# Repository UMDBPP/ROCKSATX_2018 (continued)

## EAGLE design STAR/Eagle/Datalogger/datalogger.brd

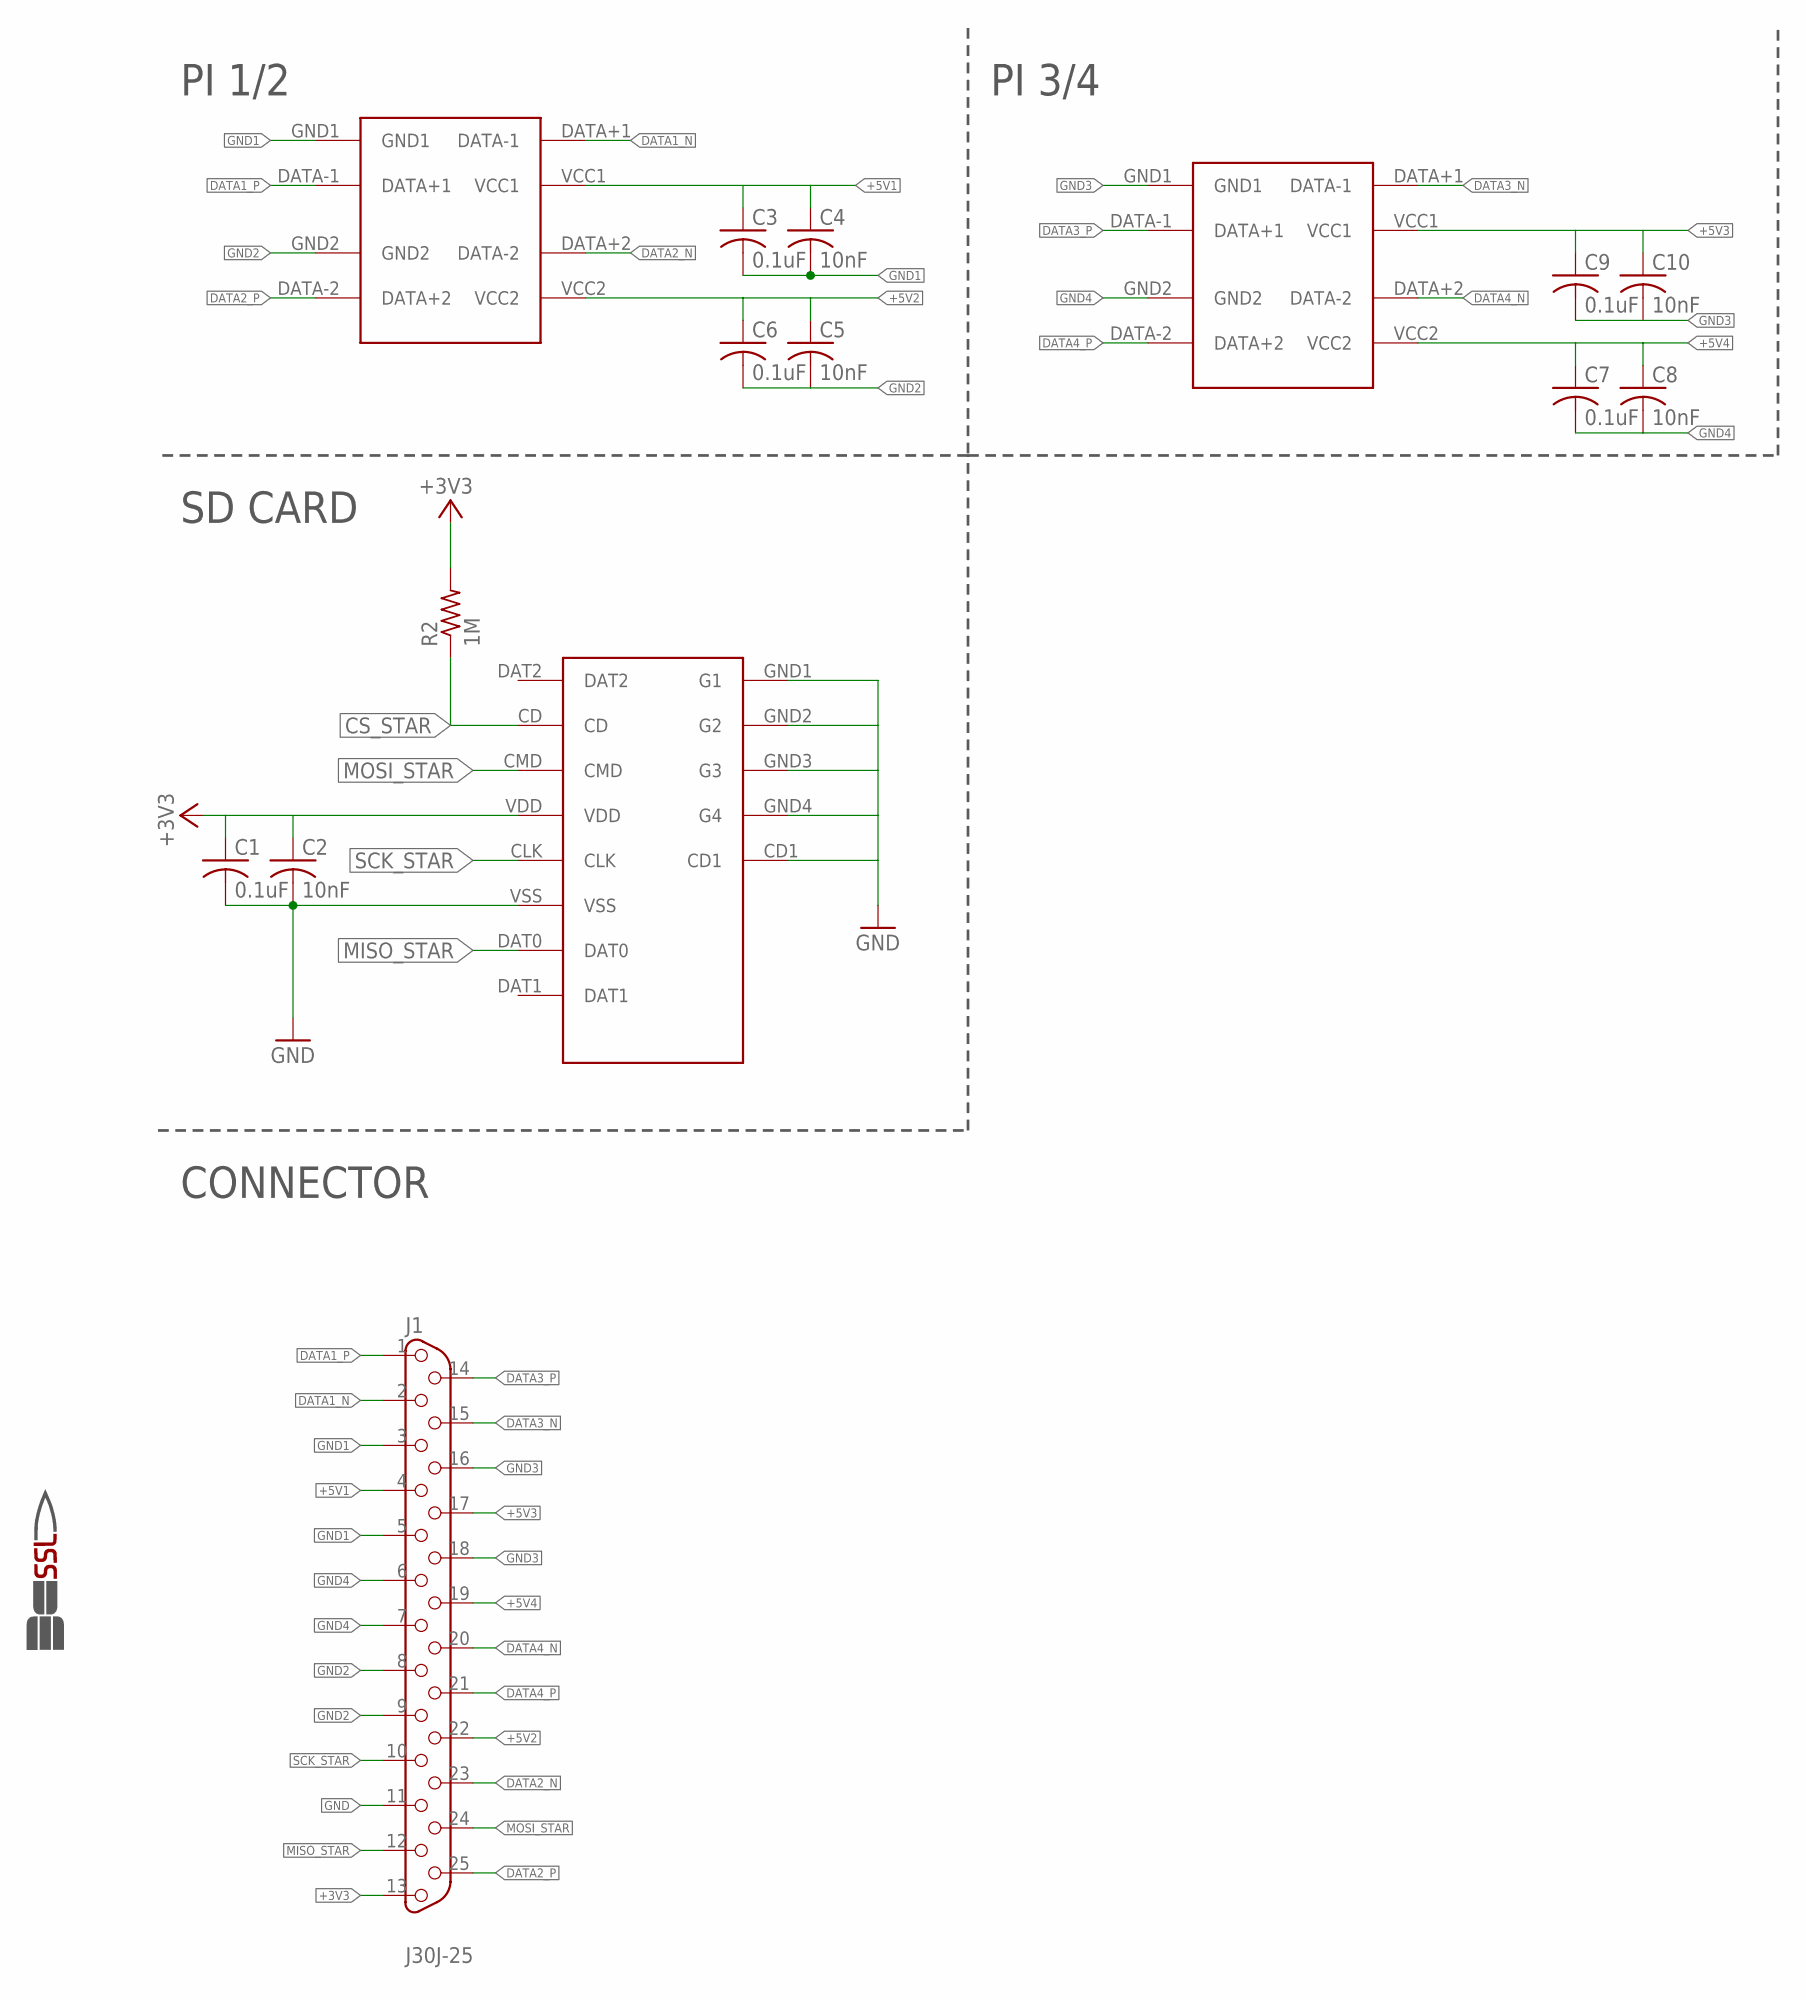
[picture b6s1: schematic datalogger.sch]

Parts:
C1, C3, C6, C7, C9: 0.1uF; C0603
C2, C4, C5, C8, C10: 10nF; C0603
GND1: SSL.3IN_SILK; SSL_SILK_.3IN
J1: J30J-25; ZKN-25
R2: 1M; R0603
U$1: MICRO_SD; MICRO_SD_HINGED
U$2, U$3: USB_A

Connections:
+3V3: C1.1, C2.1, J1.13, R2.2, U$1.VDD
+5V1: C3.1, C4.1, J1.4, U$2.VCC1
+5V2: C5.1, C6.1, J1.22, U$2.VCC2
+5V3: C9.1, C10.1, J1.17, U$3.VCC1
+5V4: C7.1, C8.1, J1.19, U$3.VCC2
CS_STAR: R2.1, U$1.CD
DATA1_N: J1.2, U$2.DATA+1 (DATA-1)
DATA1_P: J1.1, U$2.DATA-1 (DATA+1)
DATA2_N: J1.23, U$2.DATA+2 (DATA-2)
DATA2_P: J1.25, U$2.DATA-2 (DATA+2)
DATA3_N: J1.15, U$3.DATA+1 (DATA-1)
DATA3_P: J1.14, U$3.DATA-1 (DATA+1)
DATA4_N: J1.20, U$3.DATA+2 (DATA-2)
DATA4_P: J1.21, U$3.DATA-2 (DATA+2)
GND: C1.2, C2.2, J1.11, U$1.CD1, U$1.GND1 (G1), U$1.GND2 (G2), U$1.GND3 (G3), U$1.GND4 (G4), U$1.VSS
GND1: C3.2, C4.2, J1.3, J1.5, U$2.GND1
GND2: C5.2, C6.2, J1.8, J1.9, U$2.GND2
GND3: C9.2, C10.2, J1.16, J1.18, U$3.GND1
GND4: C7.2, C8.2, J1.6, J1.7, U$3.GND2
MISO_STAR: J1.12, U$1.DAT0
MOSI_STAR: J1.24, U$1.CMD
SCK_STAR: J1.10, U$1.CLK

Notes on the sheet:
PI 1/2
PI 3/4
SD CARD
CONNECTOR

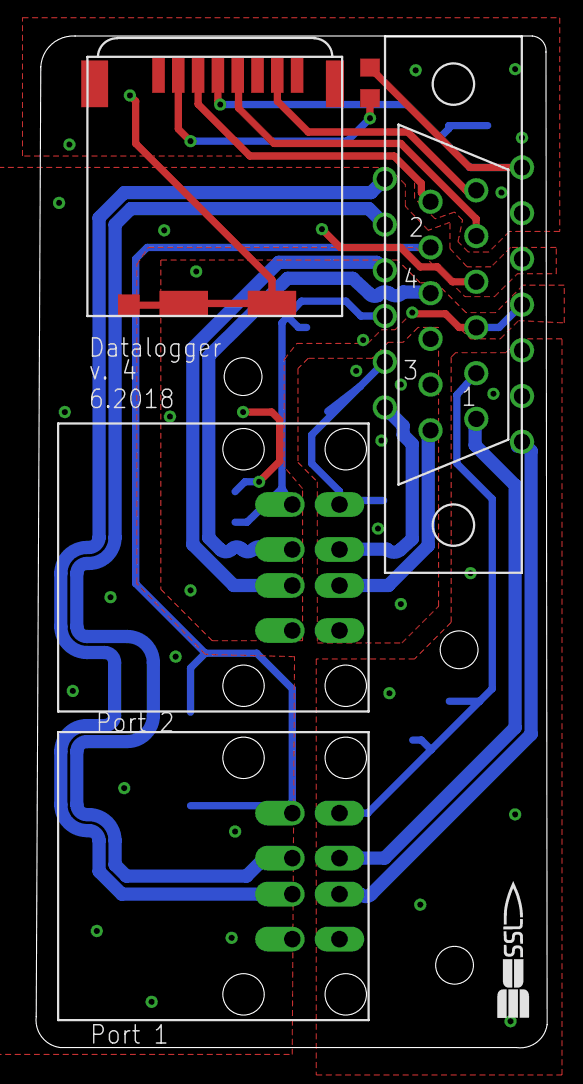
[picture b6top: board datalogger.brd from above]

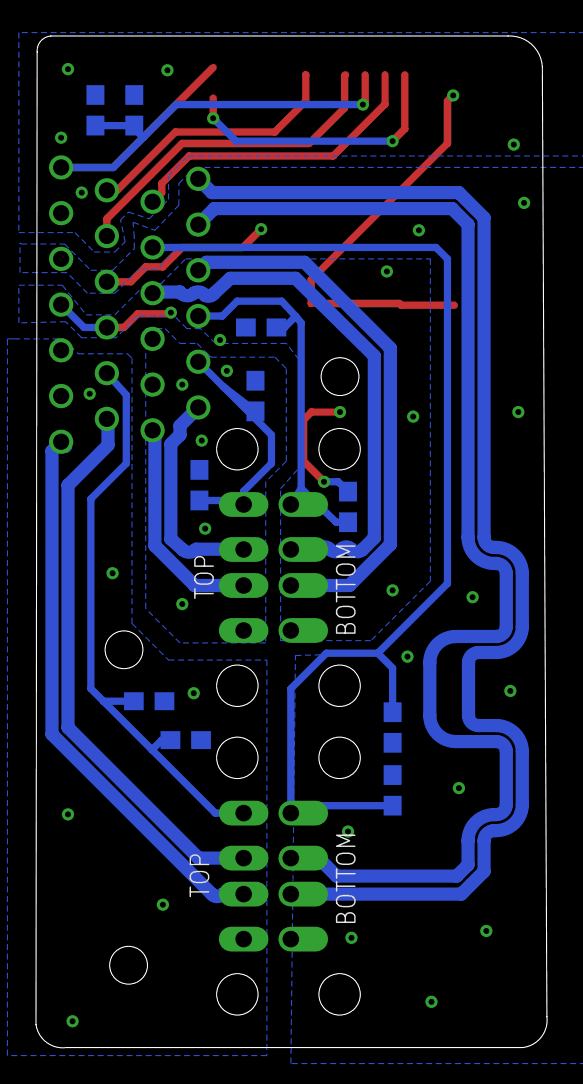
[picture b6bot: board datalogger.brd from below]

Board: 2 copper layers, 28.4 x 56.2 mm, 16 parts (10 on the bottom side), 22 nets.

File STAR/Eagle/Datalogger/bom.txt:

Partlist exported from C:/UMD/BPP/ROCKSAT X/2018/ROCKSATX_2018/STAR/Eagle/Datalogger/datalogger.sch at 7/8/2018 11:54

Qty Value        Device       Package         Parts               Description                
5   0.1uF        C-USC0603    C0603           C1, C3, C6, C7, C9  CAPACITOR, American symbol 
5   10nF         C-USC0603    C0603           C2, C4, C5, C8, C10 CAPACITOR, American symbol 
1   1M           R-US_R0603   R0603           R2                  RESISTOR, American symbol  
1   J30J-25      J30J-25      ZKN-25          J1                                             
1   MICRO_SD     MICRO_SD     MICRO_SD_HINGED U$1                                            
1   SSL.3IN_SILK SSL.3IN_SILK SSL_SILK_.3IN   GND1                                           
2   USB_A        USB_A        USB_A           U$2, U$3

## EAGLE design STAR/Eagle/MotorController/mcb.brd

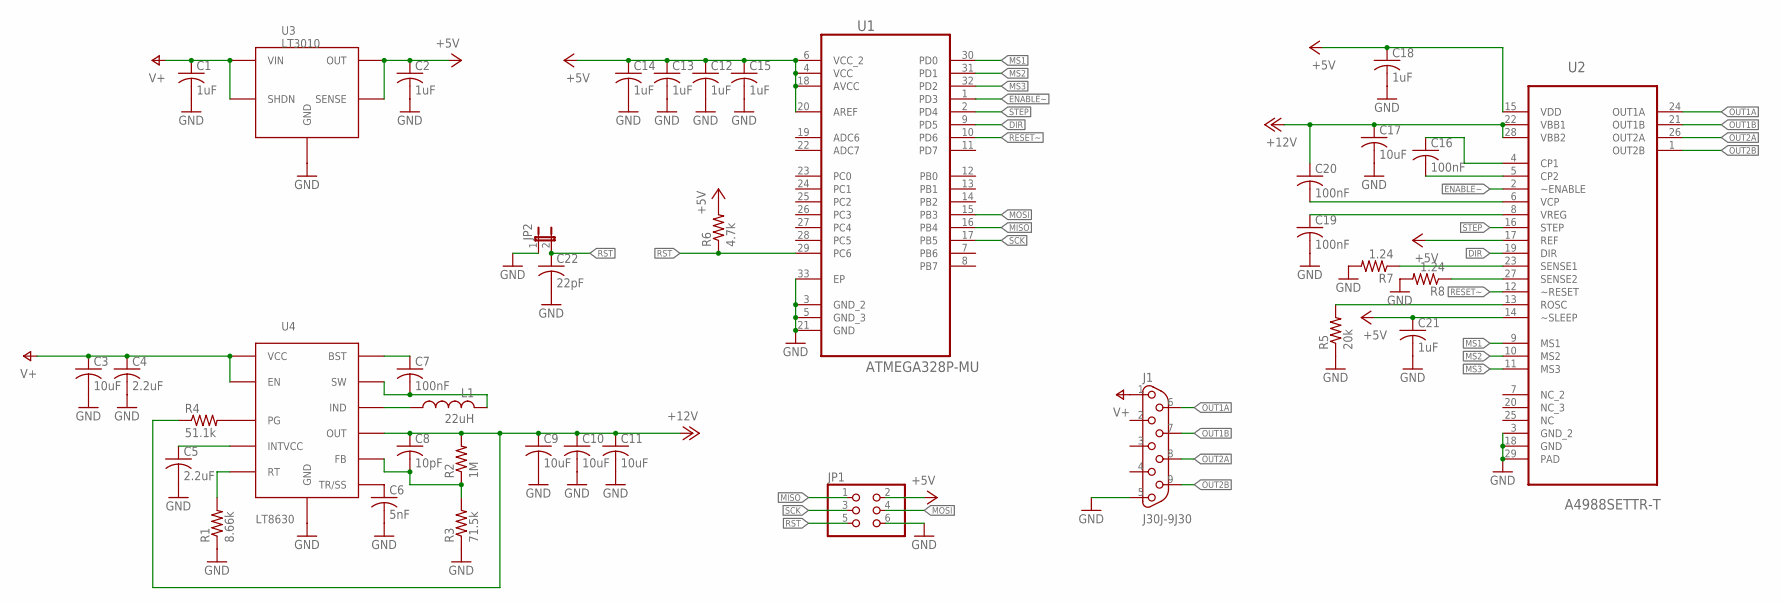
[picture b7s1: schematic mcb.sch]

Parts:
C1, C2, C12, C13, C14, C15, C18, C21: 1uF; C0603
C3, C9, C10, C11, C17: 10uF; C1206
C4, C5: 2.2uF; C0805
C6: 5nF; C0603
C7, C16, C19, C20: 100nF; C0603
C8: 10pF; C0603
C22: 22pF; C0603
J1: J30J-9J30; ZKN-9-J30
JP1: PINHD-2X3; 2X03
JP2: JUMPER-2SMD-NO; SJ_2S-NO
L1: 22uH; SRP1265A
R1: 8.66k; R0603
R2: 1M; R0603
R3: 71.5k; R0603
R4: 51.1k; R0603
R5: 20k; R0603
R6: 4.7k; R0603
R7, R8: 1.24; R0603
U1: ATMEGA328P-MU; QFN50P500X500X100-33N
U2: A4988SETTR-T; QFN50P500X500X100-29N
U3: LT3010; 8-MSOP
U4: LT8630; 20-TSSOP

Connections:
+5V: C2.1, C12.1, C13.1, C14.1, C15.1, C18.1, C21.1, JP1.2, R6.2, U1.4 (VCC), U1.6 (VCC_2), U1.18 (AVCC), U1.20 (AREF), U2.14 (~SLEEP), U2.15 (VDD), U2.17 (REF), U3.1 (OUT), U3.2 (SENSE)
+12V: C8.1, C9.1, C10.1, C11.1, C17.1, C20.1, R2.2, R4.1, U2.22 (VBB1), U2.28 (VBB2), U4.P$12 (OUT)
DIR: U1.9 (PD5), U2.19 (DIR)
ENABLE~: U1.1 (PD3), U2.2 (~ENABLE)
GND: C1.2, C2.2, C3.2, C4.2, C5.2, C6.2, C9.2, C10.2, C11.2, C12.2, C13.2, C14.2, C15.2, C17.2, C18.2, C19.2, C21.2, C22.2, J1.5, JP1.6, JP2.1, R1.1, R3.1, R5.1, R7.2, R8.2, U1.3 (GND_2), U1.5 (GND_3), U1.21 (GND), U1.33 (EP), U2.3 (GND_2), U2.18 (GND), U2.29 (PAD), U3.3 (GND), U3.4 (GND), U3.6 (GND), U3.7 (GND), U3.9 (GND), U4.P$0 (GND)
MISO: JP1.1, U1.16 (PB4)
MOSI: JP1.4, U1.15 (PB3)
MS1: U1.30 (PD0), U2.9 (MS1)
MS2: U1.31 (PD1), U2.10 (MS2)
MS3: U1.32 (PD2), U2.11 (MS3)
unnamed: C6.1, U4.P$10 (TR/SS)
unnamed: C16.1, U2.4 (CP1)
unnamed: R4.2, U4.P$5 (PG)
unnamed: C5.1, U4.P$16 (INTVCC)
unnamed: R1.2, U4.P$8 (RT)
unnamed: R7.1, U2.23 (SENSE1)
unnamed: C7.1, U4.P$18 (BST)
unnamed: C7.2, L1.P$2 (2), U4.P$20 (SW)
unnamed: C20.2, U2.6 (VCP)
unnamed: C8.2, R2.1, R3.2, U4.P$11 (FB)
unnamed: L1.P$1 (1), U4.P$14 (IND)
unnamed: C16.2, U2.5 (CP2)
unnamed: R5.2, U2.13 (ROSC)
unnamed: C19.1, U2.8 (VREG)
unnamed: R8.1, U2.27 (SENSE2)
OUT1A: J1.6, U2.24 (OUT1A)
OUT1B: J1.7, U2.21 (OUT1B)
OUT2A: J1.8, U2.26 (OUT2A)
OUT2B: J1.9, U2.1 (OUT2B)
RESET~: U1.10 (PD6), U2.12 (~RESET)
RST: C22.1, JP1.5, JP2.2, R6.1, U1.29 (PC6)
SCK: JP1.3, U1.17 (PB5)
STEP: U1.2 (PD4), U2.16 (STEP)
V+: C1.1, C3.1, C4.1, J1.1, U3.5 (SHDN), U3.8 (VIN), U4.P$1 (VCC), U4.P$3 (EN)

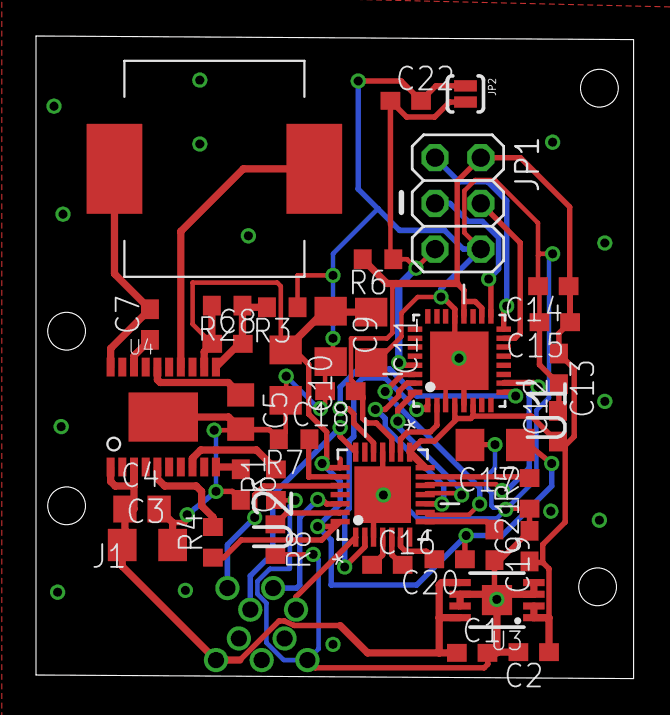
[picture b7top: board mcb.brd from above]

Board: 2 copper layers, 33.2 x 35.7 mm, 38 parts (0 on the bottom side), 34 nets.

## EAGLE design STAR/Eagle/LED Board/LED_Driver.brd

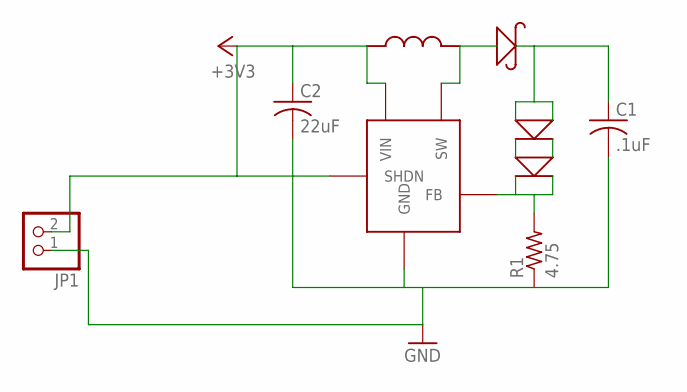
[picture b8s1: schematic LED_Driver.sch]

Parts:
C1: .1uF; C0603
C2: 22uF; C0603
JP1: PINHD-1X2; 1X02
R1: 4.75; R0603
U$1: LT1937; TSOT-23
U$2: NLCV25-PF
U$3: DB2J310
U$4, U$5: CLA2A-WKW-CYBZ0343CT

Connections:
+3V3: C2.1, JP1.2, U$1.P$4 (SHDN), U$1.P$5 (VIN), U$2.P$1
GND: C1.2, C2.2, JP1.1, R1.1, U$1.P$2 (GND)
unnamed: U$4.P$4 (GND2), U$5.P$2 (VIN2)
unnamed: U$1.P$1 (SW), U$2.P$2, U$3.P$2 (VIN)
unnamed: C1.1, U$3.P$1 (GND), U$4.P$1 (VIN1), U$4.P$2 (VIN2)
unnamed: U$4.P$3 (GND1), U$5.P$1 (VIN1)
unnamed: R1.2, U$1.P$3 (FB), U$5.P$3 (GND1), U$5.P$4 (GND2)

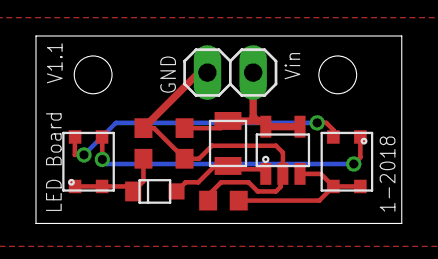
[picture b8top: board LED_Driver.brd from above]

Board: 2 copper layers, 20.3 x 10.4 mm, 9 parts (0 on the bottom side), 7 nets.

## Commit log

2017-10-17 CAD for CoDR
2017-10-17 STEP of CAD
    STEP file of the cad with colored safe zone on plate
2017-10-17 STARduino I2C fixes
2017-10-25 Added the new layout for the plater
2017-10-31 STARduino and Datalogger
2017-10-31 Datalogger and STARduino
2017-11-03 datalogger eagle and NX
2017-11-05 Add files via upload
    Added FOV for Pi Cams obtained from GrabCad
2017-11-06 scamp and shaker
    added scamp range of motion approximately. added new shaker mechanism
    with motors
2017-11-06 organized datalogger schematic
2017-11-07 STARduino MCU
2017-11-07 deleted lockfiles
2017-11-07 reorganized cad files
    moved cad files to cad folder and created folder for pdr
2017-11-07 Add files via upload
    Placeholders for stuff
2017-11-07 Add files via upload
    layout w/ pi zeros and datalogger
2017-11-07 added pi zeroes and data logger
2017-11-08 datalogger, mostly done
2017-11-10 datalogger cad
2017-11-10 New Cad
2017-11-11 STAR EBox Altered and Added to plate.
2017-11-13 Added STAR software file structure, and copied prior STARduino code
2017-11-13 Added Pi Software folder
2017-11-13 Datalogger v1 final
2017-11-13 moved stuff
2017-11-14 started cleanup
2017-11-14 added constraints moved starduino
2017-11-14 Updated CAD
2017-11-14 Update CAD
2017-11-17 CAD Cleanup
2017-11-17 fixed
2017-11-19 rotated boards
2017-11-19 added FOV
2017-11-19 made changes to ebox
2017-11-19 LED Driver Board
2017-11-19 added fasteners to pdr folder
2017-11-19 some changes to baseplate and ebox
2017-11-19 LED board, added text
2017-11-20 Updates to assembly
2017-11-20 added usb flash drives
2017-11-20 humidity sensor to STARduino
2017-11-20 added connector files
2017-11-20 led board CAD
2017-11-20 holes to datalogger
2017-11-21 removed leftovers from last year
2017-11-21 added ChipCap library
2017-11-21 started updating for 2018, added dynamic logfile naming
2017-11-21 rename ChipCap to match name of class
2017-11-21 changed header include from a library to a file
2017-11-21 small fixes to get code to compile
2017-11-24 updated assembly
2017-11-24 assembly updates
2017-11-27 LED FOV and moved stuff
2017-11-27 LED FOV
2017-11-27 Added fasteners to star ebox and pizeros
2017-11-28 31 pin connector to datalogger
2017-11-28 baseplate updated
2017-11-28 Added ports to Ebox
2017-11-28 connectors on outside of ebox
2017-11-28 moved connectors on ebox
2017-11-29 Altered starduino assembly
2017-11-29 assembly update
2017-11-29 assembly updates silicone
2017-11-29 centered shakers
2017-11-29 placed origin in center of plate
2017-11-30 changed material of plate
2017-12-01 Git cleanup
2017-12-01 moved files
2017-12-01 moved contents to higher level folders
2017-12-01 added readme
2017-12-01 removed numbers from filesnames, removed spaces
2017-12-01 continued renaming of parts and reassociation of assemblies with new part names
2017-12-01 continued rename and moving
2017-12-01 continued cleanup
2017-12-01 removed files
2017-12-01 added file naming guidelines
2017-12-03 Moved boards around
2017-12-03 altered plate
2017-12-03 added heatblock
2017-12-03 Added SCAMP Parts into SCAMP V4.1
2017-12-04 Added SCAMP to the payload plate
2017-12-04 shortened pi heat block
2017-12-04 o ring groove on ebox
2017-12-05 Added ROM CAD File
2017-12-05 Updated ROM
2017-12-05 Added SCAMP ROM and camera
2017-12-05 reconstrained stuff
2017-12-05 Moved Pizeros and edited picams
2017-12-05 added bias genboard
2017-12-05 Updated contacts
2017-12-05 moved pizeros
2017-12-05 Added STARduino voltage regulation
2017-12-05 added organizational info
2017-12-05 fixed spacing
2017-12-05 moved boards added connectors
2017-12-05 added some mechanical drawings
2017-12-05 Added ROM to SCAMP again
2017-12-05 Sunshade holes
2017-12-05 updated boards and assembly. uploaded the clip
2017-12-05 holes in sunshade
2017-12-05 CAD changes
2017-12-05 more drawings
2017-12-05 sunshade stuff
2017-12-05 bias generator schematic
2017-12-05 Changed Camera, Finished plate connect
2017-12-05 Added another D-sub for SCAMP
2017-12-05 Final SCAMP Updae pre-CDR
2017-12-05 cad things
2017-12-06 added baseplate mech
2017-12-06 uploaded some fasteners swapped screws on pizeros
2017-12-06 CAD Renders
2017-12-06 Added fasteners
2017-12-06 renders
2017-12-06 fixed routing shit on datalogger:
2017-12-21 datalogger v. 2
2017-12-23 fixed datalogger USB port
2017-12-30 datalogger differential pairs
2017-12-30 M2 drills
2018-01-02 bias gen board
2018-01-02 got rid of old STARduino routing
2018-01-03 half a routed STARduino
2018-01-04 STARduino
2018-01-08 misc board stuff
2018-01-08 Updated to final end effector shape, added O-ring seals for housings.
2018-01-09 screws
2018-01-09 Updated motor housing
2018-01-09 All sealing surfaces completed
2018-01-09 external kill
2018-01-11 .step files:
2018-01-11 got rid of log files
2018-01-11 moved stuff on STARduino
2018-01-11 Changed bearing and plate interface design
2018-01-11 Updated all of SCAMP with major changes
2018-01-12 CAD for STARduino, datalogger
2018-01-13 moved new boards in Terp assembly
2018-01-14 updated bias board cad
2018-01-15 moved boards added l brackets
2018-01-24 changes to fasteners
2018-01-25 changes to shaker rod and rotated boards
2018-01-25 added wire clips
2018-01-25 created newFOV
2018-01-25 altered assembly
2018-01-30 created rough pi extension
2018-01-30 checking material
2018-01-30 material properties
2018-01-30 more materials
2018-01-30 shaker motor weight
2018-01-30 material props
2018-01-30 added estimated fasteners
2018-01-30 NASA Update
    Starting to update the design for the NASA requirements. Will go over more in person, and the CAD is not finished yet, I just have to get to homework tonight. If there are questions let me know.
2018-01-31 Added piextension to pizero
2018-01-31 added material prop to fasteners
2018-01-31 added part
2018-01-31 updated shaker motor model
2018-02-02 update part
2018-02-02 added screw mounts for link arm
2018-02-02 dpdates materials
2018-02-02 updated payload assembly
2018-02-05 mcb update
2018-02-05 increased room for C16
2018-02-05 mounting holes on mcb
2018-02-07 weight reduction
2018-02-09 Beginning final stages of assembly and design
2018-02-11 Added holes for boards and shaker to baseplate
2018-02-11 added connectors
2018-02-11 assembly changes
2018-02-11 LIghtening payload process has begun. Also integrating all the technology needed for our new goals. I am going to continue working on this throughout the next day and a half and have everyting ready 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
2018-02-12 CAD Update
2018-02-13 All of SCAMP CAD updated- Only things left to complete are the mounting holes for contacts and electronics box as well as bolts for those. SCAMP inlcudes motor, drive shaft, harmonic drive and mass d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
    Will also create mass slide tomorrow.
2018-02-13 Did things to baseplate to solve wave linking issue
2018-02-13 Added more holes and some weight reduction. Motor is now accurately massed and all that is left to do is potentially change some colors and add holes and bolts for the contacts. Mechanical drawings a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
2018-02-13 fixed duplicates
2018-02-13 Fasteners Pt1
2018-02-13 mechanical drawings
2018-02-13 Fasteners Pt2
2018-02-13 Drawings created
2018-02-13 Fasteners Pt 3
2018-02-13 Added Camera
2018-02-14 Renderings
2018-02-14 render
2018-02-20 Removed annoying cad bits
2018-03-01 resistors on bias board
2018-03-13 datalogger 2.1
2018-03-14 rotated led boards
2018-03-15 Continued SCAMP updates
2018-03-21 Finalized dovetail joint sizing
2018-03-25 Updated Mass Movement Motors
2018-03-27 Starting to update to new and lighter mass movement system
2018-03-27 Continued with new Mass Movement System
2018-04-03 New Heat Block added
2018-04-06 Updated with linear motion carriage for mass movement
2018-04-06 Copied actual testing software from Pi
2018-04-06 Actually added working test software, ready for flight unless requirements change
2018-04-07 Updated mass shuttle integration
2018-04-19 cam for test tube holder
2018-04-20 cam for first half of test tube holder
2018-04-26 Continue updating end effector
2018-04-26 Updated retension mechanism
2018-05-08 Updated Shuttle
2018-05-08 Camera addition\
2018-05-19 CAM for some parts
2018-05-20 CAM and Datalogger 2.2
2018-05-21 changed dataloger mounting
2018-05-21 Ebox CAM
2018-05-22 Added connectors!
2018-05-23 Added Pi Zero Desktop corresponding to disk image created 5/23/18
2018-05-23 Link to flight software image added
2018-05-23 Renamed flgiht software image as html file
2018-05-27 added drawing of sunshade
2018-06-02 moved rocket connectors and some wire clamps
2018-06-08 Fixed sunshade fastener holes
2018-06-08 I don't even know anymore
2018-06-08 put flange on sunshade
2018-06-08 rounded corners
2018-06-08 more rounded corners
2018-06-09 updated shaker disk and link arm
    will now use a set screw and an oil bearing for easier machening
2018-06-10 holes
2018-06-11 changed sheetmetal part sunshade
2018-06-29 Datalogger v4
2018-07-01 new board sizes
2018-07-07 Power Board
2018-07-07 new filtering caps for power board
2018-07-07 Added other bias design ideas'
2018-07-07 Fixed the three terminal capacitor routing (five capacitors).
2018-07-07 half done bias board
2018-07-07 resistor library
2018-07-08 Added analog isolator to bias and revised connector
2018-07-08 fixed choke routing on power board
2018-07-08 Finished routing new bias board rev 2.0. Fixed the choke configuration on that board.
2018-07-08 gerbers for boards
2018-07-08 I think I fixed all of the GSE_GND being '+3V3_FILT' but I don't know how that happened in the first place
2018-07-08 no lockfiles
2018-07-08 Fixed Blaire's nonsense on the power board. No longer shorting 3V3 to GSE_GND. The input names still make no sense
2018-07-08 Fixed all the wire stubs on Starduino
2018-07-09 Updated calculations for switching regulator
2018-07-09 New inductors for the power board, changed the error message on the values script and added CBEs. Because who needs sleep
2018-07-09 gerbers
2018-07-14 updated constraints
2018-07-21 updated bom with order
2018-07-22 Updated bias board and libraries to reflect the actual package used by the analog isolator
2018-07-22 reoriented capacitors on power board
2018-07-22 Fixed an air wire on the ground lines and a non-connection in the sketch
2018-07-22 starduino shield for M0 becuase custom boards don't always work
2018-07-23 Fixed optoisolator circuit and added SPI header on top, but not yet the SPI head on the ICSP board. Fixed a lot of air wires
2018-07-23 Added ICSP header and finished reviewing starduino
2018-07-24 STARduino sheild. Updated holes, resistor size, added some names to components to make assembly easier
2018-07-24 gerbers for power and bias board
2018-07-29 Added new holes for Arduino M0 and slide rod tapped holes
2018-08-05 Modified starduino software to suit what we think we ar eusing this year. Commented out a ton of nonsense.
2018-08-05 Updates o software
2018-08-06 M0_PreFlight2018
    Writes more than one line to file now. Closes data logging file after a time
2018-08-06 MotorFlight_Aug6
    Uncommmented timing interrupts for motor activation
2018-08-10 FLIGHT CODE as of the moment we passed it off for check-in
2018-08-30 fixes to cad
2018-08-31 updates to cad
2018-09-21 added renders
2018-09-30 Some Renders
2018-09-30 renders and such
2018-09-30 OMG more renders
2018-10-20 adding renders and some changes I noticed I didnt push yet
